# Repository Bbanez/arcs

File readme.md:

# ARCS Devices #

ARCS stands for Automation and Robotics Control System. Goal of ARCS is to bring new generation of PLC to the market. ARCS devices will have industrial grade quality and will be able to replace old traditional PLC devices with little modifications to exiting systems. In addition to this, ARCS devices will be easy to connect in a network, support new generation of IoT, easily scalable, allow advanced monitoring with modern GUI and OpenGL graphics, implementation of traditional programing methods like BASIC/C and Leader Logic and introduction of new programing logic that is more intuitive and easy to learn.

ARCS devices are divided into three groups:

- Processing Devices (PD) - This group of devices are used for processing data, implementing control logic and generating control signals. It could be say that ARCS-PD is replacement for PLC.
- Module Devices (MD) - This group of devices are used to expend features of ARCS-PD. For example to expend I/O capabilities, allow GSM connection, allow connection of special type of sensor...
- Utility Devices (UD) - This group of devices are used to expend back-end capabilities of ARCS. For example, signal repeaters, communication security devices, port extenders...

## ARCS-PD ##

- ARCS-PD-T-1C200R4X3M2X6 - RPI
- ARCS-PD-M-0C216R320M1X3 - F746ZG
- ARCS-PD-M-0C180R128M512 - F446RE
- ARCS-PD-M-0C072R020M064 - F103C8
- ARCS-PD-L-0C016R008M256 - 2560
- ARCS-PD-L-0C016R002M032 - 328P, 328PB, 32u4

> Notation

```
	a-cCccRrrrMmmm
	|   |   |   |
	|   |   |   -> Storage size in megabytes
	|   |   -----> RAM memory size in megabytes
	|   ---------> CPU frequency in gigahertz
	-------------> Rank
```

## ARCS-MD ##

- ARCS-MD-IGP-A04 - General purpose 4 analog input module.
- ARCS-MD-IGP-A08 - General purpose 8 analog input module.
- ARCS-MD-IGP-A16 - General purpose 16 analog input module.
- ARCS-MD-IGP-A32 - General purpose 32 analog input module.
- ARCS-MD-IGP-D04 - General purpose 4 digital input module.
- ARCS-MD-IGP-D08 - General purpose 8 digital input module.
- ARCS-MD-IGP-D16 - General purpose 16 digital input module.
- ARCS-MD-IGP-D32 - General purpose 32 digital input module.
- ARCS-MD-OGP-A04 - General purpose 4 analog output module.
- ARCS-MD-OGP-A08 - General purpose 8 analog output module.
- ARCS-MD-OGP-A16 - General purpose 16 analog output module.
- ARCS-MD-OGP-A32 - General purpose 32 analog output module.
- ARCS-MD-OGP-D04 - General purpose 4 digital output module.
- ARCS-MD-OGP-D08 - General purpose 8 digital output module.
- ARCS-MD-OGP-D16 - General purpose 16 digital output module.
- ARCS-MD-OGP-D32 - General purpose 32 digital output module.
- ARCS-MD-GSM - 
- ARCS-MD-ETH - 
- ARCS-MD-NB - 
- ARCS-MD-WIFI -

## ARCS-UD ##

- ARCS-UD-TWCLREP1 - 
- ARCS-UD-TWCLREP2 - 
- ARCS-UD-TWCLSEC - 
- ARCS-UD-SEC16 - 
- ARCS-UD-SEC32 -
- ARCS-UD-BAT25 - 
- ARCS-UD-BAT50 - 
- ARCS-UD-BAT100 - 
- ARCS-UD-BAT200 -

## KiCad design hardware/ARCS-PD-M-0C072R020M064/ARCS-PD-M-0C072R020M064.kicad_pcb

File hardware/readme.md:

# ARCS Devices #

ARCS stands for Automation and Robotics Control System. Goal of ARCS is to bring new generation of PLC to the market. ARCS devices will have industrial grade quality and will be able to replace old traditional PLC devices with little modifications to exiting infrastructure. In addition to this, ARCS devices will be easy to connect in a network, support new generation of IoT, easily scalable, allow advanced monitoring with modern GUI and OpenGL graphics, implementation of traditional programing methods like BASIC/C and Leader Logic and introduction of new programing logic that is more intuitive and easy to learn.

ARCS devices are divided into three groups:

- Processing Devices (PD) - This group of devices are used for processing data, implementing control logic and generating control signals. It could be say that ARCS-PD is replacement for PLC.
- Module Devices (MD) - This group of devices are used to expend features of ARCS-PD. For example to expend I/O capabilities, allow GSM connection, allow connection of special type of sensor...
- Utility Devices (UD) - This group of devices are used to expend back-end capabilities of ARCS. For example, signal repeaters, communication security devices, port extenders...

## ARCS-PD ##

- ARCS-PD-T-1C200R4X3M2X6 - RPI
- ARCS-PD-M-0C216R320M1X3 - F746ZG
- ARCS-PD-M-0C180R128M512 - F446RE
- ARCS-PD-M-0C072R020M064 - F103C8
- ARCS-PD-L-0C016R008M256 - 2560
- ARCS-PD-L-0C016R002M032 - 328P, 328PB, 32u4

> Notation

```
	a-cCccRrrrMmmm
	|   |   |   |
	|   |   |   -> Storage size in megabytes
	|   |   -----> RAM memory size in megabytes
	|   ---------> CPU frequency in gigahertz
	-------------> Rank
```

## ARCS-MD ##

- ARCS-MD-IGP-A04 - General purpose 4 analog input module.
- ARCS-MD-IGP-A08 - General purpose 8 analog input module.
- ARCS-MD-IGP-A16 - General purpose 16 analog input module.
- ARCS-MD-IGP-A32 - General purpose 32 analog input module.
- ARCS-MD-IGP-D04 - General purpose 4 digital input module.
- ARCS-MD-IGP-D08 - General purpose 8 digital input module.
- ARCS-MD-IGP-D16 - General purpose 16 digital input module.
- ARCS-MD-IGP-D32 - General purpose 32 digital input module.
- ARCS-MD-OGP-A04 - General purpose 4 analog output module.
- ARCS-MD-OGP-A08 - General purpose 8 analog output module.
- ARCS-MD-OGP-A16 - General purpose 16 analog output module.
- ARCS-MD-OGP-A32 - General purpose 32 analog output module.
- ARCS-MD-OGP-D04 - General purpose 4 digital output module.
- ARCS-MD-OGP-D08 - General purpose 8 digital output module.
- ARCS-MD-OGP-D16 - General purpose 16 digital output module.
- ARCS-MD-OGP-D32 - General purpose 32 digital output module.
- ARCS-MD-GSM - 
- ARCS-MD-ETH - 
- ARCS-MD-NB - 
- ARCS-MD-WIFI -

## ARCS-UD ##

- ARCS-UD-TWCLREP1 - 
- ARCS-UD-TWCLREP2 - 
- ARCS-UD-TWCLSEC - 
- ARCS-UD-SEC16 - 
- ARCS-UD-SEC32 -
- ARCS-UD-BAT25 - 
- ARCS-UD-BAT50 - 
- ARCS-UD-BAT100 - 
- ARCS-UD-BAT200 -

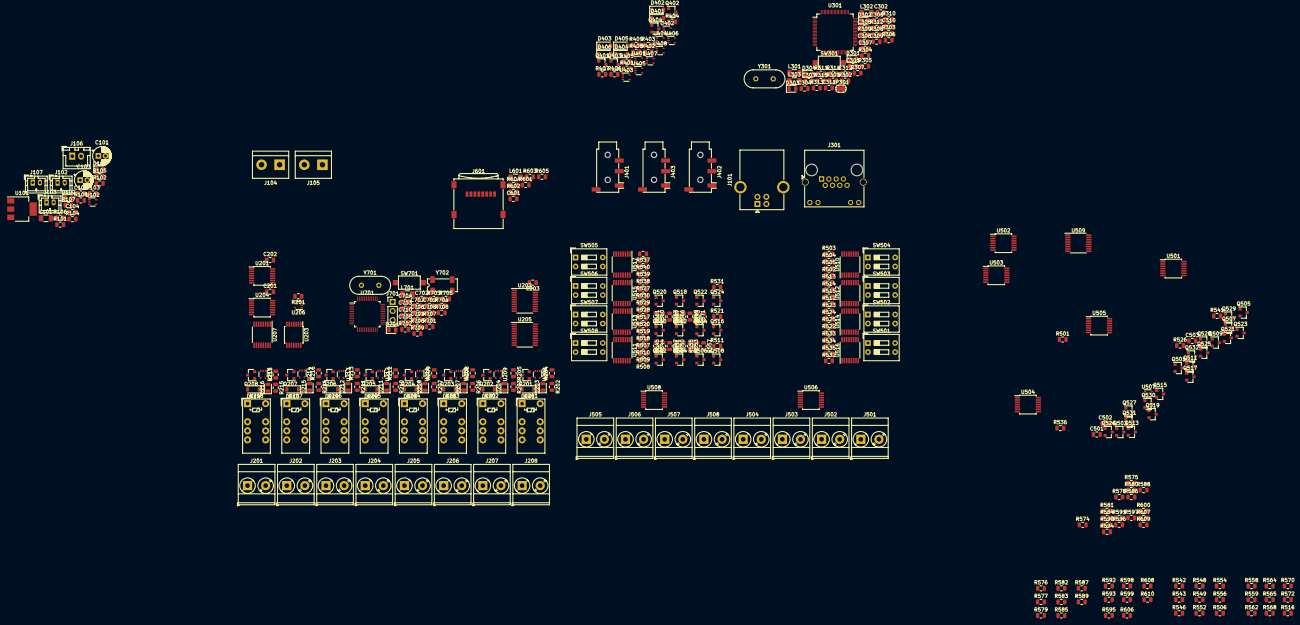
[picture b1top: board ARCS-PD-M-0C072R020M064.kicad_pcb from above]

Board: 2 copper layers, 375 parts (0 on the bottom side), 363 nets, no tracks yet.

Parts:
C101, C103: 47u; CP_Radial_D5.0mm_P2.00mm
C102, C104, C201, C202, C203, C302, C303, C304, C305, C307, C308, C309, C310, C501, C502, C503, C601, C705, C706, C707, C708, C709, C710: 100n; C_0805_2012Metric
C301, C306: 10u; C_0805_2012Metric
C311, C312: 18p; C_0805_2012Metric
C701, C702, C703, C704: 22p; C_0805_2012Metric
D101, D303: LED_RED; LED_0805_2012Metric
D102, D302: LED_YELLOW; LED_0805_2012Metric
D201, D202, D205, D206, D209, D210, D213, D214, D401, D402, D403, D404, D405, D406: 1N4007; D_SOD-123
D203, D204, D207, D208, D211, D212, D215, D216, D301, D304: LED_GREEN; LED_0805_2012Metric
D701: LED_ALT; LED_0805_2012Metric
J101: USB_B; USB_B_OST_USB-B1HSxx_Horizontal
J102, J103, J107: Conn_01x02; JST_PH_B2B-PH-K_1x02_P2.00mm_Vertical
J104, J105: Conn_01x02_PWR; TerminalBlock_bornier-2_P5.08mm
J106: JST-XH-01X02; JST_XH_B02B-XH-A_1x02_P2.50mm_Vertical
J201, J202, J203, J204, J205, J206, J207, J208: Conn_01x02; TerminalBlock_Phoenix_MKDS-3-2-5.08_1x02_P5.08mm_Horizontal
J301: RJ45_LED_Shielded; RJ45_Amphenol_RJHSE538X
J401, J402, J403: XLR3_Ground; Jack_3.5mm_PJ320D_Horizontal
J501, J502, J503, J504, J505, J506, J507, J508: Input_Terminal_01x02; TerminalBlock_Phoenix_MKDS-3-2-5.08_1x02_P5.08mm_Horizontal
J601: Micro_SD_Card; microSD_HC_Wuerth_693072010801
J701: Conn_01x03; PinHeader_1x03_P2.54mm_Vertical
JP301: SolderJumper_2_Open; SolderJumper-2_P1.3mm_Open_RoundedPad1.0x1.5mm
K201, K202, K203, K204, K205, K206, K207, K208: G6S-2; Relay_DPDT_Omron_G6S-2
L101: Ferrite_Bead; R_1206_3216Metric
L301, L302, L303, L601, L701: 1u; L_1206_3216Metric
Q201, Q202, Q203, Q204, Q205, Q206, Q207, Q208, Q401, Q402, Q403, Q404: 2N7002; SOT-23
Q501, Q502, Q503, Q504, Q505, Q506, Q507, Q508, Q509, Q510, Q511, Q512, Q513, Q514, Q515, Q516, Q517, Q518, Q519, Q520, Q521, Q522, Q523, Q524, Q525, Q526, Q527, Q528, Q529, Q530, Q531, Q532: PMBT3906; SOT-23
R101: 0; R_0805_2012Metric
R102, R103: 27; R_0805_2012Metric
R104, R105, R108, R311, R313, R314, R315, R404, R405, R406, R407, R408, R409, R502, R503, R504, R505, R507, R508, R509, R510, R512, R513, R514, R515, R517, R518, R519, R520, R522, R523, R524, R525, R527, R528, R529, R530, R532, R533, R534, R535, R537, R538, R539, R540: 1k; R_0805_2012Metric
R106, R107, R554, R555, R570, R571, R586, R587, R607, R608: 1k5; R_0805_2012Metric
R201, R202, R203, R206, R207, R210, R211, R214, R215, R307, R308, R401, R402, R403, R501, R506, R511, R516, R521, R526, R531, R536, R541, R601, R602, R603, R604, R605, R707, R708, R709: 10k; R_0805_2012Metric
R204, R205, R208, R209, R212, R213, R216, R217, R706: 4k7; R_0805_2012Metric
R301, R302: 330; R_0805_2012Metric
R303, R304, R305, R306: 49.9; R_0805_2012Metric
R309: 12k; R_0805_2012Metric
R310: 300; R_0805_2012Metric
R312, R701: 1M; R_0805_2012Metric
R542, R544, R558, R560, R574, R576, R590, R592: 62k; R_0805_2012Metric
R543, R545, R559, R561, R575, R577, R591, R593: 480; R_0805_2012Metric
R546, R547, R562, R563, R578, R579, R594, R595: 43; R_0805_2012Metric
R548, R550, R564, R566, R580, R582, R596, R598: 24k; R_0805_2012Metric
R549, R551, R565, R567, R581, R583, R597, R599: 2k2; R_0805_2012Metric
R552, R553, R568, R569, R584, R585, R600, R606: 160; R_0805_2012Metric
R556, R557, R572, R573, R588, R589, R609, R610: 15; R_0805_2012Metric
R702, R703, R704, R705: 100k; R_0805_2012Metric
SW301, SW701: SW_Push; SW_SPST_CK_RS282G05A3
SW501, SW502, SW503, SW504, SW505, SW506, SW507, SW508: SW_DIP_x02; SW_DIP_SPSTx02_Slide_9.78x7.26mm_W7.62mm_P2.54mm
U101: AMS1117-3.3; SOT-223-3_TabPin2
U102, U206, U208, U209, U210, U211, U212, U213, U214, U215, U401, U402, U404, U405, U406, U507: 74LVC1G125; SOT-353_SC-70-5
U201, U204, U504, U505: 74HC74; TSSOP-14_4.4x5mm_P0.65mm
U202, U205: 74HC374; TSSOP-20_4.4x6.5mm_P0.65mm
U203, U501: 74HC00; TSSOP-14_4.4x5mm_P0.65mm
U207, U509, U510, U511, U512, U513, U514, U515, U516, U517: 74HC4051; TSSOP-16_4.4x5mm_P0.65mm
U301: W5100; LQFP-80_10x10mm_P0.4mm
U403, U407, U408: 74LVC1G00; SOT-353_SC-70-5
U502, U503, U506, U508: LM324; TSSOP-14_4.4x5mm_P0.65mm
U701: STM32F103C8Tx; LQFP-48_7x7mm_P0.5mm
Y301: 25MHz; Crystal_HC49-4H_Vertical
Y701: 8MHz; Crystal_HC49-4H_Vertical
Y702: 32k-MC306; Crystal_SMD_SeikoEpson_MC306-4Pin_8.0x3.2mm

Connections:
+3V3: C101.1, C102.1, C103.1, C104.1, C201.2, C202.2, C203.1, C301.1, C302.1, C303.1, C304.1, C305.1, C501.2, C502.2, C503.1, C601.1, C707.1, C708.1, C709.1, D201.1, D202.1, D205.1, D206.1, D209.1, D210.1, D213.1, D214.1, D401.1, D402.1, D403.1, D404.1, D405.1, D406.1, J105.1, J601.4, K201.1, K202.1, K203.1, K204.1, K205.1, K206.1, K207.1, K208.1, L303.1, L701.1, R104.1, R105.1, R106.1, R107.1, R108.1, R201.1, R202.1, R203.1, R204.1, R205.1, R206.1, R207.1, R208.1, R209.1, R210.1, R211.1, R212.1, R213.1, R214.1, R215.1, R216.1, R217.1, R301.1, R302.1, R307.1, R308.1, R311.1, R313.1, R314.1, R315.1, R401.1, R402.1, R403.1, R404.1, R405.1, R406.1, R407.1, R408.1, R409.1, R501.1, R601.1, R602.1, R603.1, R604.1, R605.1, R703.2, R705.2, R706.2, R707.1, R709.1, U101.2, U101.3, U102.5, U201.4, U201.10, U201.14, U202.20, U203.14, U204.4, U204.10, U204.14, U205.20, U206.5, U207.16, U208.5, U209.5, U210.5, U211.5, U212.5, U213.5, U214.5, U215.5, U301.12, U301.18, U301.44, U401.5, U402.5, U403.2, U403.5, U404.5, U405.5, U406.5, U407.2, U407.5, U408.2, U408.5, U501.14, U504.4, U504.10, U504.14, U505.4, U505.10, U505.14, U506.4, U507.5, U508.4, U509.16, U510.3, U510.16, U511.3, U511.16, U512.3, U512.16, U513.3, U513.16, U514.3, U514.16, U515.3, U515.16, U516.3, U516.16, U517.3, U517.16, U701.24, U701.36, U701.48
+24V: J104.1, U502.4, U503.4
/Sheet5BC1BC85/PA1: D102.1, J107.2, U701.11
/Sheet5BC1BC85/PA6: D101.1, J103.2, U701.16
/Sheet5BC1BC85/PC13: D701.1, J102.2, U701.2
/Sheet5E10F3BC/1V8: L302.1, U301.11, U301.15, U301.16, U301.33, U301.69
/Sheet5E10F3BC/1V8A: L302.2, U301.7, U301.74
/Sheet5E10F3BC/3V3A: C306.1, C308.1, C309.1, J301.3, J301.6, L303.2, U301.2
/Sheet5E10F3BC/FDXLED: J301.9, U301.70
/Sheet5E10F3BC/LINKLED: J301.11, U301.66
/Sheet5E10F3BC/RXIN: J301.2, R304.2, U301.6
/Sheet5E10F3BC/RXIP: J301.1, R306.2, U301.5
/Sheet5E10F3BC/TXON: J301.8, R303.2, U301.9
/Sheet5E10F3BC/TXOP: J301.7, R305.2, U301.8
ETH-CS: U301.29, U701.17
GND: C101.2, C102.2, C103.2, C104.2, C201.1, C202.1, C203.2, C301.2, C302.2, C303.2, C304.2, C305.2, C306.2, C307.2, C308.2, C309.2, C310.2, C311.2, C312.2, C501.1, C502.1, C503.2, C601.2, C701.2, C702.2, C703.2, C704.2, C705.1, C706.2, C707.2, C708.2, C709.2, C710.2, J101.4, J104.2, J105.2, J601.6, J701.3, JP301.1, K201.9, K202.9, K203.9, K204.9, K205.9, K206.9, K207.9, K208.9, L301.2, L601.2, Q201.2, Q202.2, Q203.2, Q204.2, Q205.2, Q206.2, Q207.2, Q208.2, Q401.2, Q402.2, Q403.2, Q404.2, R101.1, R310.2, R506.2, R511.2, R516.2, R521.2, R526.2, R531.2, R536.2, R541.2, R702.2, R704.2, R708.2, SW301.1, SW701.2, U101.1, U102.1, U102.3, U201.7, U202.1, U202.10, U203.7, U204.7, U205.1, U205.10, U206.1, U206.3, U207.6, U207.7, U207.8, U208.1, U208.3, U209.1, U209.3, U210.1, U210.3, U211.1, U211.3, U212.1, U212.3, U213.1, U213.3, U214.1, U214.3, U215.1, U215.3, U301.4, U301.10, U301.13, U301.14, U301.17, U301.32, U301.34, U301.35, U301.36, U301.37, U301.43, U301.63, U301.64, U301.65, U301.68, U301.77, U401.1, U401.3, U402.1, U402.3, U403.3, U404.1, U404.3, U405.1, U405.3, U406.1, U406.3, U407.3, U408.3, U501.7, U502.11, U503.11, U504.7, U505.7, U506.11, U507.1, U507.3, U508.11, U509.6, U509.7, U509.8, U510.6, U510.7, U510.8, U510.9, U511.6, U511.7, U511.8, U511.9, U512.6, U512.7, U512.8, U512.9, U513.6, U513.7, U513.8, U513.9, U514.6, U514.7, U514.8, U514.9, U515.6, U515.7, U515.8, U515.9, U516.6, U516.7, U516.8, U516.9, U517.6, U517.7, U517.8, U517.9, U701.8, U701.23, U701.35, U701.47, Y702.2, Y702.3
I2C-SCL: J106.2, R106.2, U701.45
I2C-SDA: J106.1, R107.2, U701.46
IG1I: U509.3, U701.10
IG1IS: U505.3, U701.28
IG1ISF: U501.11, U701.43
unnamed: C307.1, R304.1, R306.1
unnamed: C310.1, R303.1, R305.1
unnamed: C311.1, R312.2, U301.75, Y301.1
unnamed: C312.1, R312.1, U301.76, Y301.2
unnamed: C701.1, R701.2, U701.5, Y701.1
unnamed: C702.1, R701.1, U701.6, Y701.2
unnamed: C703.1, U701.3, Y702.1
unnamed: C704.1, U701.4, Y702.4
unnamed: C705.2, R707.2, SW701.1, U701.7
unnamed: C706.1, U701.1
unnamed: C710.1, L701.2, U701.9
unnamed: D101.2, J103.1, R105.2
unnamed: D102.2, J107.1, R108.2
unnamed: D201.2, K201.12, Q201.3
unnamed: D202.2, K202.12, Q202.3
unnamed: D203.1, K201.8, R202.2, U207.4
unnamed: D203.2, R204.2
unnamed: D204.1, K202.8, R203.2, U207.2
unnamed: D204.2, R205.2
unnamed: D205.2, K203.12, Q203.3
unnamed: D206.2, K204.12, Q204.3
unnamed: D207.1, K203.8, R206.2, U207.5
unnamed: D207.2, R208.2
unnamed: D208.1, K204.8, R207.2, U207.1
unnamed: D208.2, R209.2
unnamed: D209.2, K205.12, Q205.3
unnamed: D210.2, K206.12, Q206.3
unnamed: D211.1, K205.8, R210.2, U207.12
unnamed: D211.2, R212.2
unnamed: D212.1, K206.8, R211.2, U207.15
unnamed: D212.2, R213.2
unnamed: D213.2, K207.12, Q207.3
unnamed: D214.2, K208.12, Q208.3
unnamed: D215.1, K207.8, R214.2, U207.14
unnamed: D215.2, R216.2
unnamed: D216.1, K208.8, R215.2, U207.13
unnamed: D216.2, R217.2
unnamed: D301.1, U301.73
unnamed: D301.2, R311.2
unnamed: D302.1, U301.72
unnamed: D302.2, R313.2
unnamed: D303.1, U301.71
unnamed: D303.2, R314.2
unnamed: D304.1, U301.67
unnamed: D304.2, R315.2
unnamed: D701.2, R706.1
unnamed: J101.1, L101.2
unnamed: J101.2, R102.2
unnamed: J101.3, R103.2
unnamed: J101.5, R101.2
unnamed: J102.1, R104.2
unnamed: J301.10, R302.2
unnamed: J301.12, R301.2
unnamed: J301.SH, L301.1
unnamed: J501.1, U506.12
unnamed: J501.2, J502.2, J503.2, J504.2
unnamed: J502.1, U506.10
unnamed: J503.1, U506.5
unnamed: J504.1, U506.3
unnamed: J505.1, U508.3
unnamed: J505.2, J506.2, J507.2, J508.2
unnamed: J506.1, U508.5
unnamed: J507.1, U508.10
unnamed: J508.1, U508.12
unnamed: J601.1, R605.2
unnamed: J601.8, R601.2
unnamed: J601.9, L601.1
unnamed: J701.1, R708.1, U701.34
unnamed: J701.2, R709.2, U701.37
unnamed: JP301.2, R307.2, U301.31
unnamed: L101.1, U102.2
unnamed: Q201.1, U208.4
unnamed: Q202.1, U209.4
unnamed: Q203.1, U210.4
unnamed: Q204.1, U211.4
unnamed: Q205.1, U212.4
unnamed: Q206.1, U213.4
unnamed: Q207.1, U214.4
unnamed: Q208.1, U215.4
unnamed: Q401.1, U403.4
unnamed: Q402.1, U404.4
unnamed: Q403.1, U407.4
unnamed: Q404.1, U408.4
unnamed: Q501.1, R505.1
unnamed: Q501.2, Q503.2, Q505.2, Q507.2, U506.1, U506.2
unnamed: Q501.3, R542.2
unnamed: Q502.1, R510.1
unnamed: Q502.2, Q504.2, Q506.2, Q508.2, U508.1, U508.2
unnamed: Q502.3, R544.2
unnamed: Q503.1, R504.1
unnamed: Q503.3, R548.2
unnamed: Q504.1, R509.1
unnamed: Q504.3, R550.2
unnamed: Q505.1, R503.1
unnamed: Q505.3, R554.2
unnamed: Q506.1, R508.1
unnamed: Q506.3, R555.2
unnamed: Q507.1, R502.1
unnamed: Q507.3, R506.1, R546.1, R552.1, R556.1, U503.3
unnamed: Q508.1, R507.1
unnamed: Q508.3, R511.1, R547.1, R553.1, R557.1, U502.3
unnamed: Q509.1, R515.1
unnamed: Q509.2, Q511.2, Q513.2, Q515.2, U506.6, U506.7
unnamed: Q509.3, R558.2
unnamed: Q510.1, R520.1
unnamed: Q510.2, Q512.2, Q514.2, Q516.2, U508.6, U508.7
unnamed: Q510.3, R560.2
unnamed: Q511.1, R514.1
unnamed: Q511.3, R564.2
unnamed: Q512.1, R519.1
unnamed: Q512.3, R566.2
unnamed: Q513.1, R513.1
unnamed: Q513.3, R570.2
unnamed: Q514.1, R518.1
unnamed: Q514.3, R571.2
unnamed: Q515.1, R512.1
unnamed: Q515.3, R516.1, R562.1, R568.1, R572.1, U503.5
unnamed: Q516.1, R517.1
unnamed: Q516.3, R521.1, R563.1, R569.1, R573.1, U502.5
unnamed: Q517.1, R525.1
unnamed: Q517.2, Q519.2, Q521.2, Q523.2, U506.8, U506.9
unnamed: Q517.3, R574.2
unnamed: Q518.1, R530.1
unnamed: Q518.2, Q520.2, Q522.2, Q524.2, U508.8, U508.9
unnamed: Q518.3, R576.2
unnamed: Q519.1, R524.1
unnamed: Q519.3, R580.2
unnamed: Q520.1, R529.1
unnamed: Q520.3, R582.2
unnamed: Q521.1, R523.1
unnamed: Q521.3, R586.2
unnamed: Q522.1, R528.1
unnamed: Q522.3, R587.2
unnamed: Q523.1, R522.1
unnamed: Q523.3, R526.1, R578.1, R584.1, R588.1, U503.10
unnamed: Q524.1, R527.1
unnamed: Q524.3, R531.1, R579.1, R585.1, R589.1, U502.10
unnamed: Q525.1, R535.1
unnamed: Q525.2, Q527.2, Q529.2, Q531.2, U506.13, U506.14
unnamed: Q525.3, R590.2
unnamed: Q526.1, R540.1
unnamed: Q526.2, Q528.2, Q530.2, Q532.2, U508.13, U508.14
unnamed: Q526.3, R592.2
unnamed: Q527.1, R534.1
unnamed: Q527.3, R596.2
unnamed: Q528.1, R539.1
unnamed: Q528.3, R598.2
unnamed: Q529.1, R533.1
unnamed: Q529.3, R607.2
unnamed: Q530.1, R538.1
unnamed: Q530.3, R608.2
unnamed: Q531.1, R532.1
unnamed: Q531.3, R536.1, R594.1, R600.1, R609.1, U503.12
unnamed: Q532.1, R537.1
unnamed: Q532.3, R541.1, R595.1, R606.1, R610.1, U502.12
unnamed: R201.2, U201.1, U201.13, U204.1, U204.13, U206.4
unnamed: R308.2, SW301.2, U301.59
unnamed: R309.1, U301.1
unnamed: R309.2, R310.1
unnamed: R501.2, U504.1, U504.13, U505.1, U505.13, U507.4
unnamed: R502.2, U510.12
unnamed: R503.2, U510.15
unnamed: R504.2, U510.14
unnamed: R505.2, U510.13
unnamed: R507.2, U511.12
unnamed: R508.2, U511.15
unnamed: R509.2, U511.14
unnamed: R510.2, U511.13
unnamed: R512.2, U512.12
unnamed: R513.2, U512.15
unnamed: R514.2, U512.14
unnamed: R515.2, U512.13
unnamed: R517.2, U513.12
unnamed: R518.2, U513.15
unnamed: R519.2, U513.14
unnamed: R520.2, U513.13
unnamed: R522.2, U514.12
unnamed: R523.2, U514.15
unnamed: R524.2, U514.14
unnamed: R525.2, U514.13
unnamed: R527.2, U515.12
unnamed: R528.2, U515.15
unnamed: R529.2, U515.14
unnamed: R530.2, U515.13
unnamed: R532.2, U516.12
unnamed: R533.2, U516.15
unnamed: R534.2, U516.14
unnamed: R535.2, U516.13
unnamed: R537.2, U517.12
unnamed: R538.2, U517.15
unnamed: R539.2, U517.14
unnamed: R540.2, U517.13
unnamed: R542.1, R543.2
unnamed: R543.1, R546.2
unnamed: R544.1, R545.2
unnamed: R545.1, R547.2
unnamed: R548.1, R549.2
unnamed: R549.1, R552.2
unnamed: R550.1, R551.2
unnamed: R551.1, R553.2
unnamed: R554.1, R556.2
unnamed: R555.1, R557.2
unnamed: R558.1, R559.2
unnamed: R559.1, R562.2
unnamed: R560.1, R561.2
unnamed: R561.1, R563.2
unnamed: R564.1, R565.2
unnamed: R565.1, R568.2
unnamed: R566.1, R567.2
unnamed: R567.1, R569.2
unnamed: R570.1, R572.2
unnamed: R571.1, R573.2
unnamed: R574.1, R575.2
unnamed: R575.1, R578.2
unnamed: R576.1, R577.2
unnamed: R577.1, R579.2
unnamed: R580.1, R581.2
unnamed: R581.1, R584.2
unnamed: R582.1, R583.2
unnamed: R583.1, R585.2
unnamed: R586.1, R588.2
unnamed: R587.1, R589.2
unnamed: R590.1, R591.2
unnamed: R591.1, R594.2
unnamed: R592.1, R593.2
unnamed: R593.1, R595.2
unnamed: R596.1, R597.2
unnamed: R597.1, R600.2
unnamed: R598.1, R599.2
unnamed: R599.1, R606.2
unnamed: R607.1, R609.2
unnamed: R608.1, R610.2
unnamed: R702.1, R703.1, U701.20
unnamed: R704.1, R705.1, U701.44
unnamed: SW501.1, SW501.2, SW502.1, SW502.2, SW503.1, SW503.2, SW504.1, SW504.2
unnamed: SW501.3, U516.10
unnamed: SW501.4, U516.11
unnamed: SW502.3, U514.10
unnamed: SW502.4, U514.11
unnamed: SW503.3, U512.10
unnamed: SW503.4, U512.11
unnamed: SW504.3, U510.10
unnamed: SW504.4, U510.11
unnamed: SW505.1, SW505.2, SW506.1, SW506.2, SW507.1, SW507.2, SW508.1, SW508.2
unnamed: SW505.3, U517.10
unnamed: SW505.4, U517.11
unnamed: SW506.3, U515.10
unnamed: SW506.4, U515.11
unnamed: SW507.3, U513.10
unnamed: SW507.4, U513.11
unnamed: SW508.3, U511.10
unnamed: SW508.4, U511.11
unnamed: U201.5, U203.10, U207.11
unnamed: U201.9, U203.2, U207.10
unnamed: U201.2, U201.6, U201.11
unnamed: U201.8, U201.12, U204.3
unnamed: U202.2, U202.4, U205.3
unnamed: U202.5, U202.7, U205.4
unnamed: U202.6, U202.8, U205.7
unnamed: U202.12, U202.14, U205.13
unnamed: U202.9, U202.13, U205.8
unnamed: U202.15, U202.17, U205.14
unnamed: U202.16, U202.18, U205.17
unnamed: U202.19, U205.18
unnamed: U203.1, U204.5, U207.9
unnamed: U203.3, U203.4, U203.5
unnamed: U203.6, U203.9
unnamed: U203.8, U203.12, U203.13
unnamed: U204.2, U204.6, U204.11
unnamed: U204.8, U204.12, U206.2
unnamed: U205.2, U215.2
unnamed: U205.5, U214.2
unnamed: U205.6, U213.2
unnamed: U205.9, U212.2
unnamed: U205.12, U211.2
unnamed: U205.15, U210.2
unnamed: U205.16, U209.2
unnamed: U205.19, U208.2
unnamed: U501.1, U504.5, U509.9
unnamed: U501.2, U505.9, U509.10
unnamed: U501.3, U501.4, U501.5
unnamed: U501.6, U501.9
unnamed: U501.10, U505.5, U509.11
unnamed: U501.8, U501.12, U501.13
unnamed: U502.1, U502.2, U509.13
unnamed: U502.6, U502.7, U509.14
unnamed: U502.8, U502.9, U509.15
unnamed: U502.13, U502.14, U509.12
unnamed: U503.1, U503.2, U509.1
unnamed: U503.6, U503.7, U509.5
unnamed: U503.8, U503.9, U509.2
unnamed: U503.13, U503.14, U509.4
unnamed: U504.3, U505.8, U505.12
unnamed: U504.2, U504.6, U504.11
unnamed: U504.8, U504.12, U507.2
unnamed: U505.2, U505.6, U505.11
OG1COF: U201.3, U701.25
OG1COFCF: U203.11, U701.18
OG1O01: J201.1, K208.4
OG1O02: J201.2, K208.5
OG1O11: J202.1, K207.4
OG1O12: J202.2, K207.5
OG1O21: J203.1, K206.4
OG1O22: J203.2, K206.5
OG1O31: J204.1, K205.4
OG1O32: J204.2, K205.5
OG1O41: J205.1, K204.4
OG1O42: J205.2, K204.5
OG1O51: J206.1, K203.4
OG1O52: J206.2, K203.5
OG1O61: J207.1, K202.4
OG1O62: J207.2, K202.5
OG1O71: J208.1, K201.4
OG1O72: J208.2, K201.5
OG1OSC: U202.11, U701.26
OG1OSF: U207.3, U701.19
OG1OSL: U205.11, U701.42
OG1OSS: U202.3, U701.27
SPI1-CS: J601.2, R604.2, U701.38
SPI1-MISO: J601.7, R602.2, U301.27, U701.40
SPI1-MOSI: J601.3, R603.2, U301.28, U701.41
SPI1-SCK: J601.5, U301.30, U701.39
T1-RX: D403.2, J401.2, R406.2, U405.2
T1-SB: D405.2, J401.3, R408.2
T1-TX: D401.2, J401.1, Q403.3, R404.2
T2-RX: J402.2, Q401.3
T2-SB: J402.3, Q402.3, U402.2
T2-SBI: U402.4, U701.15
T2-SBO: U404.2, U701.14
T2-TX: J402.1, U401.2
T3-RX: D404.2, J403.2, R407.2, U406.2
T3-SB: D406.2, J403.3, R409.2
T3-TX: D402.2, J403.1, Q404.3, R405.2
UART1-RX: U405.4, U701.31
UART1-TX: R402.2, U407.1, U701.30
UART2-RX: U401.4, U701.13
UART2-TX: R401.2, U403.1, U701.12
UART3-RX: U406.4, U701.22
UART3-TX: R403.2, U408.1, U701.21
USB-DM: R102.1, U701.32
USB-DP: R103.1, U701.33
USB-PWR: U102.4, U701.29
